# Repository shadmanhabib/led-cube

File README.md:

# LED-Cube
Repository of LED Cube project.

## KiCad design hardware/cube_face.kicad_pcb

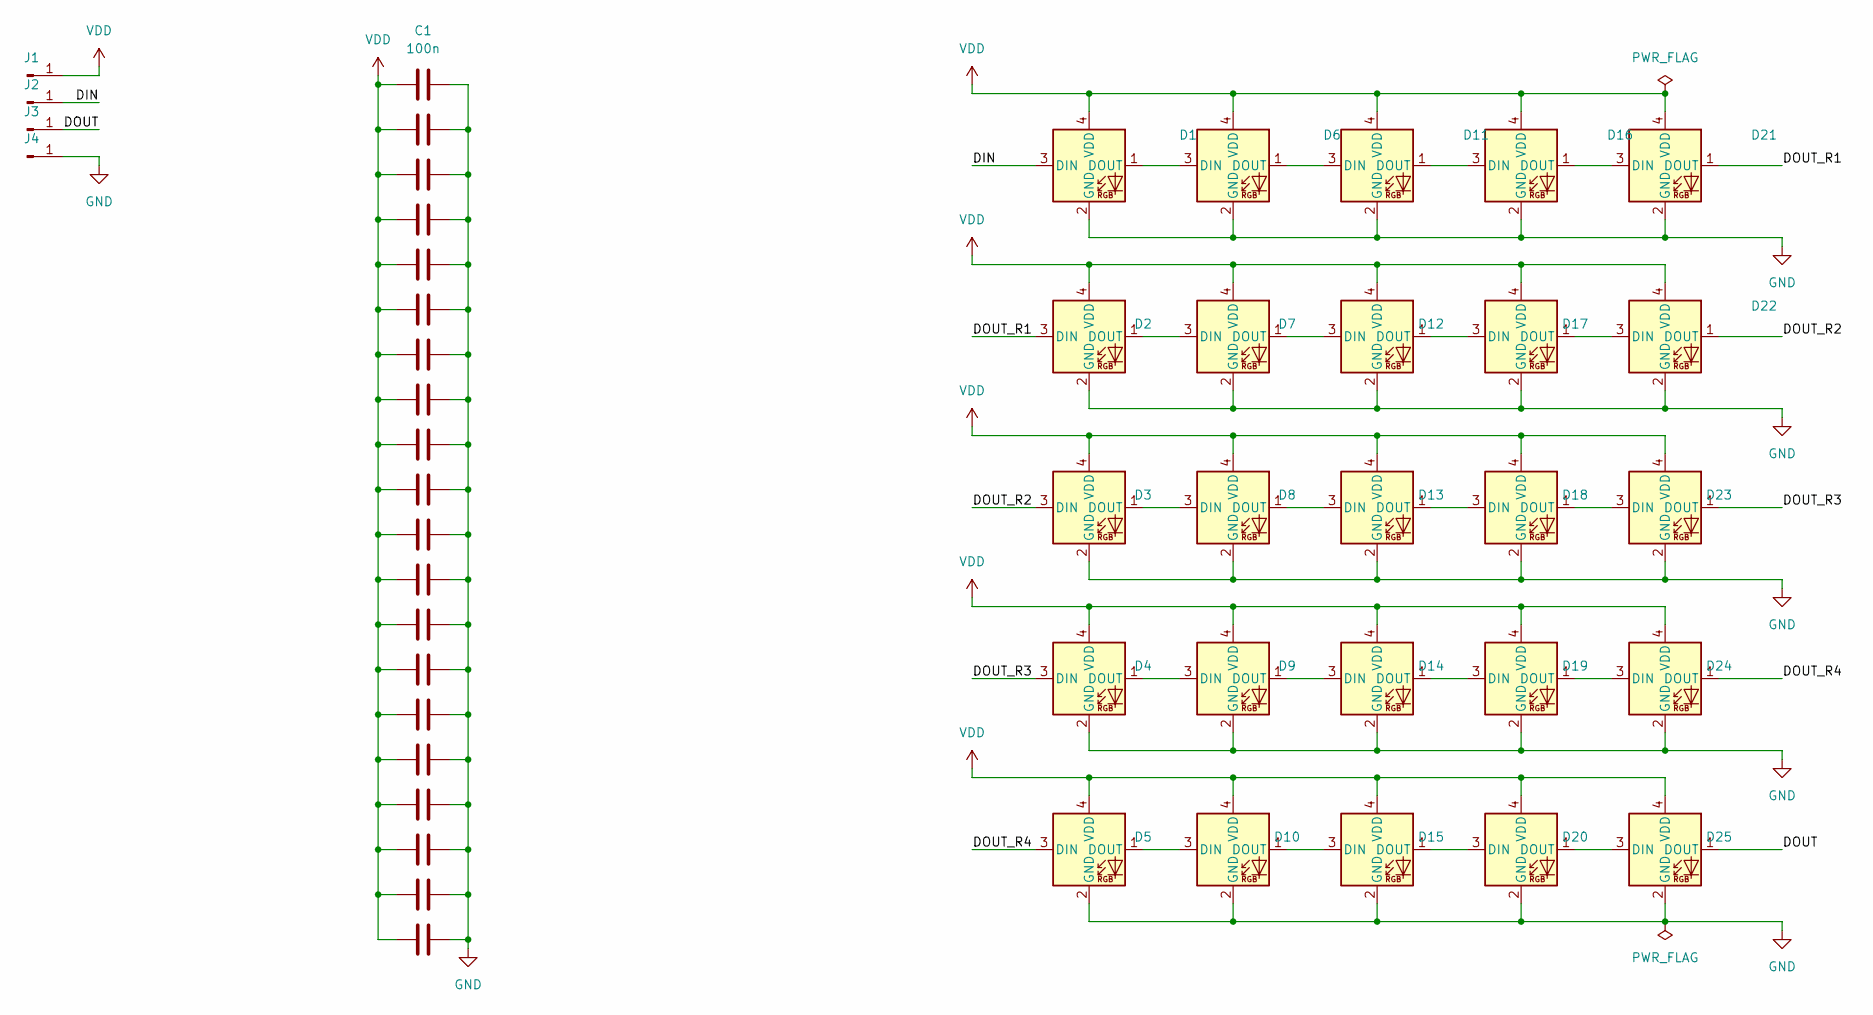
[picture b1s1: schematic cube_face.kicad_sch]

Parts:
C1, C2, C3, C4, C5, C6, C7, C8, C9, C10, C11, C12, C13, C14, C15, C16, C17, C18, C19, C20: 100n; C_0603_1608Metric
D1, D2, D3, D4, D5, D6, D7, D8, D9, D10, D11, D12, D13, D14, D15, D16, D17, D18, D19, D20, D21, D22, D23, D24, D25: WS2812B-2020
J1, J2, J3, J4: Conn_01x01_Male; SolderWirePad_1x01_SMD_5x10mm

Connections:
/DIN: D1.3 (DIN), J2.1
/DOUT: D25.1 (DOUT), J3.1
/DOUT_R1: D2.3 (DIN), D21.1 (DOUT)
/DOUT_R2: D3.3 (DIN), D22.1 (DOUT)
/DOUT_R3: D4.3 (DIN), D23.1 (DOUT)
/DOUT_R4: D5.3 (DIN), D24.1 (DOUT)
GND: C1.2, C2.2, C3.2, C4.2, C5.2, C6.2, C7.2, C8.2, C9.2, C10.2, C11.2, C12.2, C13.2, C14.2, C15.2, C16.2, C17.2, C18.2, C19.2, C20.2, D1.2 (GND), D2.2 (GND), D3.2 (GND), D4.2 (GND), D5.2 (GND), D6.2 (GND), D7.2 (GND), D8.2 (GND), D9.2 (GND), D10.2 (GND), D11.2 (GND), D12.2 (GND), D13.2 (GND), D14.2 (GND), D15.2 (GND), D16.2 (GND), D17.2 (GND), D18.2 (GND), D19.2 (GND), D20.2 (GND), D21.2 (GND), D22.2 (GND), D23.2 (GND), D24.2 (GND), D25.2 (GND), J4.1
unnamed: D1.1 (DOUT), D6.3 (DIN)
unnamed: D2.1 (DOUT), D7.3 (DIN)
unnamed: D3.1 (DOUT), D8.3 (DIN)
unnamed: D4.1 (DOUT), D9.3 (DIN)
unnamed: D10.1 (DOUT), D15.3 (DIN)
unnamed: D5.1 (DOUT), D10.3 (DIN)
unnamed: D11.1 (DOUT), D16.3 (DIN)
unnamed: D6.1 (DOUT), D11.3 (DIN)
unnamed: D12.1 (DOUT), D17.3 (DIN)
unnamed: D7.1 (DOUT), D12.3 (DIN)
unnamed: D13.1 (DOUT), D18.3 (DIN)
unnamed: D8.1 (DOUT), D13.3 (DIN)
unnamed: D14.1 (DOUT), D19.3 (DIN)
unnamed: D9.1 (DOUT), D14.3 (DIN)
unnamed: D15.1 (DOUT), D20.3 (DIN)
unnamed: D16.1 (DOUT), D21.3 (DIN)
unnamed: D17.1 (DOUT), D22.3 (DIN)
unnamed: D18.1 (DOUT), D23.3 (DIN)
unnamed: D19.1 (DOUT), D24.3 (DIN)
unnamed: D20.1 (DOUT), D25.3 (DIN)
VDD: C1.1, C2.1, C3.1, C4.1, C5.1, C6.1, C7.1, C8.1, C9.1, C10.1, C11.1, C12.1, C13.1, C14.1, C15.1, C16.1, C17.1, C18.1, C19.1, C20.1, D1.4 (VDD), D2.4 (VDD), D3.4 (VDD), D4.4 (VDD), D5.4 (VDD), D6.4 (VDD), D7.4 (VDD), D8.4 (VDD), D9.4 (VDD), D10.4 (VDD), D11.4 (VDD), D12.4 (VDD), D13.4 (VDD), D14.4 (VDD), D15.4 (VDD), D16.4 (VDD), D17.4 (VDD), D18.4 (VDD), D19.4 (VDD), D20.4 (VDD), D21.4 (VDD), D22.4 (VDD), D23.4 (VDD), D24.4 (VDD), D25.4 (VDD), J1.1

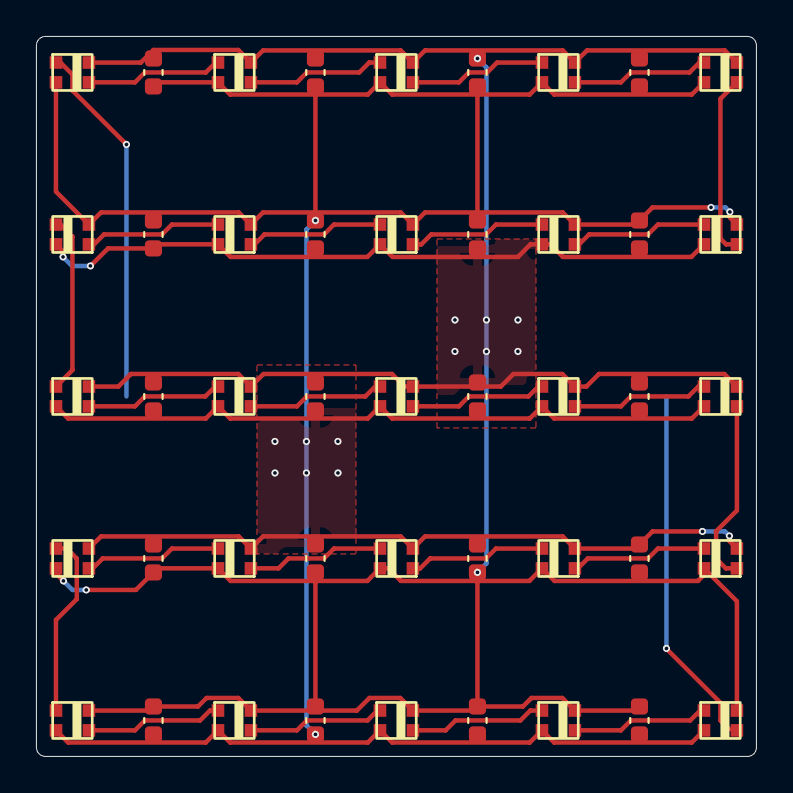
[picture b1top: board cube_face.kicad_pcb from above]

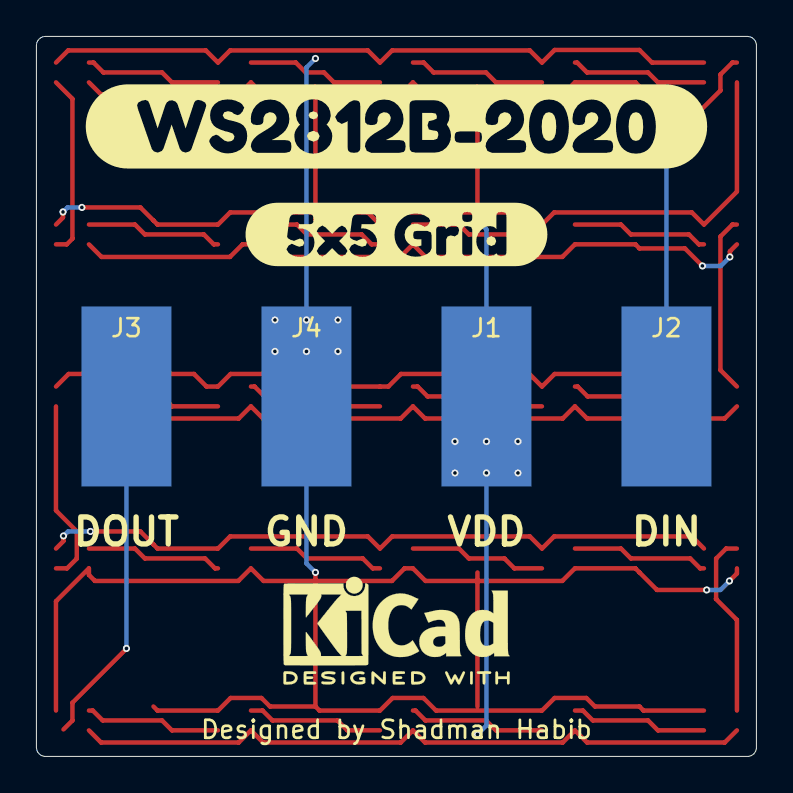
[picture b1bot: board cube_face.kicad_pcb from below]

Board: 2 copper layers, 40.0 x 40.0 mm, 51 parts (6 on the bottom side), 28 nets.

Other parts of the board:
kibuzzard-6351D6C0: G***; kibuzzard-6351D6C0
kibuzzard-6351D6F9: G***; kibuzzard-6351D6F9

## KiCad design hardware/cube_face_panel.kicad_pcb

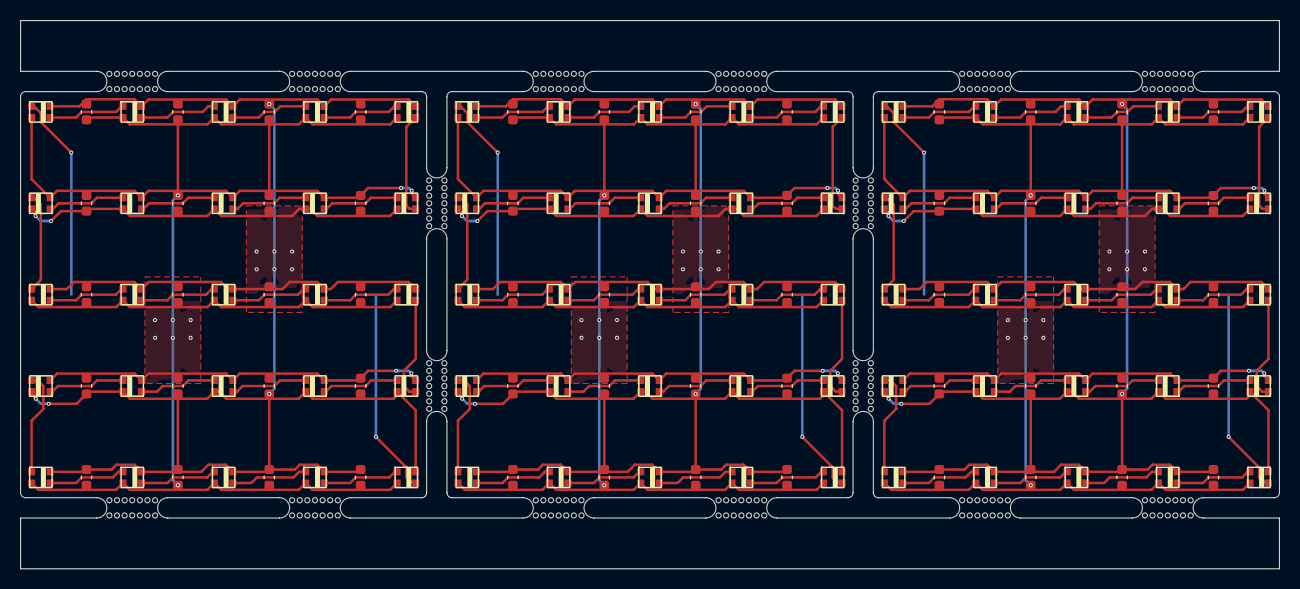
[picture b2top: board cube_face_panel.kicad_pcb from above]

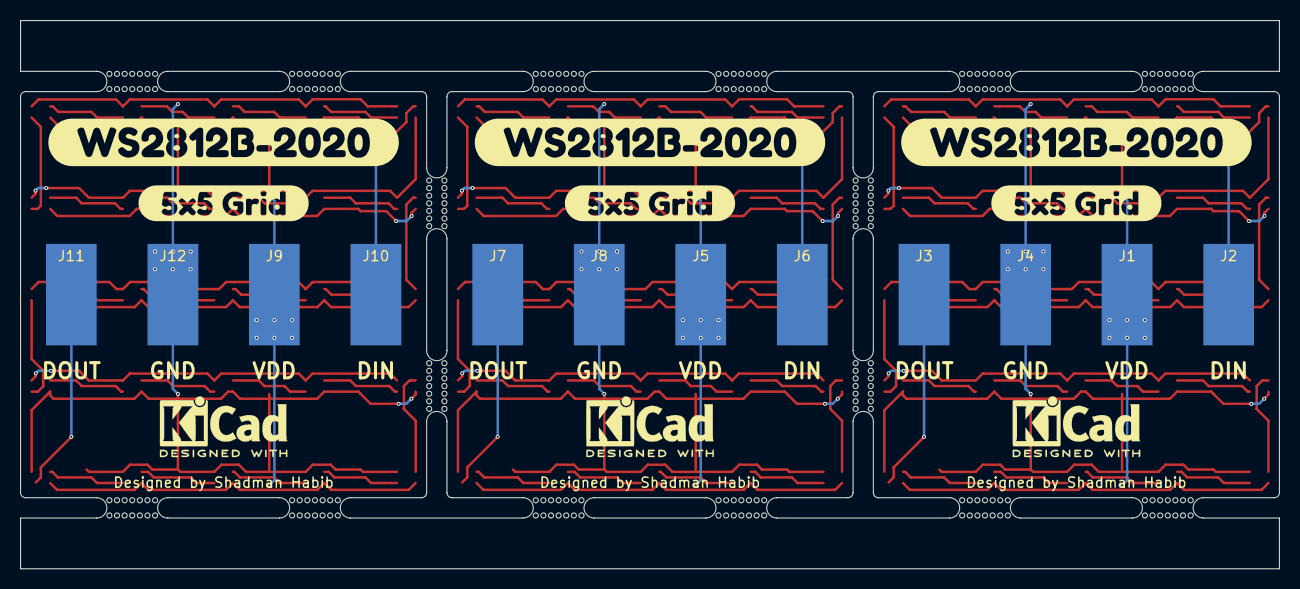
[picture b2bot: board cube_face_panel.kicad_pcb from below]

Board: 2 copper layers, 124.0 x 54.0 mm, 169 parts (18 on the bottom side), 28 nets.

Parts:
C1, C2, C3, C4, C5, C6, C7, C8, C9, C10, C11, C12, C13, C14, C15, C16, C17, C18, C19, C20, C21, C22, C23, C24, C25, C26, C27, C28, C29, C30, C31, C32, C33, C34, C35, C36, C37, C38, C39, C40, C41, C42, C43, C44, C45, C46, C47, C48, C49, C50, C51, C52, C53, C54, C55, C56, C57, C58, C59, C60: 100n; C_0603_1608Metric
D1, D2, D3, D4, D5, D6, D7, D8, D9, D10, D11, D12, D13, D14, D15, D16, D17, D18, D19, D20, D21, D22, D23, D24, D25, D26, D27, D28, D29, D30, D31, D32, D33, D34, D35, D36, D37, D38, D39, D40, D41, D42, D43, D44, D45, D46, D47, D48, D49, D50, D51, D52, D53, D54, D55, D56, D57, D58, D59, D60, D61, D62, D63, D64, D65, D66, D67, D68, D69, D70, D71, D72, D73, D74, D75: WS2812B-2020
J1, J2, J3, J4, J5, J6, J7, J8, J9, J10, J11, J12: Conn_01x01_Male; SolderWirePad_1x01_SMD_5x10mm
kibuzzard-6351D6C0, kibuzzard-6351D6C1, kibuzzard-6351D6C2: G***; kibuzzard-6351D6C0
kibuzzard-6351D6F1, kibuzzard-6351D6F2, kibuzzard-6351D6F9: G***; kibuzzard-6351D6F9
mouse-bite-2mm-slot, mouse-bite-2mm-slot#2, mouse-bite-2mm-slot#3, mouse-bite-2mm-slot#4, mouse-bite-2mm-slot#5, mouse-bite-2mm-slot#6, mouse-bite-2mm-slot#7, mouse-bite-2mm-slot#8, mouse-bite-2mm-slot#9, mouse-bite-2mm-slot#10, mouse-bite-2mm-slot#11, mouse-bite-2mm-slot#12, mouse-bite-2mm-slot#13, mouse-bite-2mm-slot#14, mouse-bite-2mm-slot#15, mouse-bite-2mm-slot#16: VAL**; mouse-bite-2mm-slot

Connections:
/DIN: D1.3 (DIN), D26.3 (DIN), D51.3 (DIN), J2.1, J6.1, J10.1
/DOUT: D25.1 (DOUT), D50.1 (DOUT), D75.1 (DOUT), J3.1, J7.1, J11.1
/DOUT_R1: D2.3 (DIN), D21.1 (DOUT), D27.3 (DIN), D46.1 (DOUT), D52.3 (DIN), D71.1 (DOUT)
/DOUT_R2: D3.3 (DIN), D22.1 (DOUT), D28.3 (DIN), D47.1 (DOUT), D53.3 (DIN), D72.1 (DOUT)
/DOUT_R3: D4.3 (DIN), D23.1 (DOUT), D29.3 (DIN), D48.1 (DOUT), D54.3 (DIN), D73.1 (DOUT)
/DOUT_R4: D5.3 (DIN), D24.1 (DOUT), D30.3 (DIN), D49.1 (DOUT), D55.3 (DIN), D74.1 (DOUT)
GND: C1.2, C2.2, C3.2, C4.2, C5.2, C6.2, C7.2, C8.2, C9.2, C10.2, C11.2, C12.2, C13.2, C14.2, C15.2, C16.2, C17.2, C18.2, C19.2, C20.2, C21.2, C22.2, C23.2, C24.2, C25.2, C26.2, C27.2, C28.2, C29.2, C30.2, C31.2, C32.2, C33.2, C34.2, C35.2, C36.2, C37.2, C38.2, C39.2, C40.2, C41.2, C42.2, C43.2, C44.2, C45.2, C46.2, C47.2, C48.2, C49.2, C50.2, C51.2, C52.2, C53.2, C54.2, C55.2, C56.2, C57.2, C58.2, C59.2, C60.2, D1.2 (GND), D2.2 (GND), D3.2 (GND), D4.2 (GND), D5.2 (GND), D6.2 (GND), D7.2 (GND), D8.2 (GND), D9.2 (GND), D10.2 (GND), D11.2 (GND), D12.2 (GND), D13.2 (GND), D14.2 (GND), D15.2 (GND), D16.2 (GND), D17.2 (GND), D18.2 (GND), D19.2 (GND), D20.2 (GND), D21.2 (GND), D22.2 (GND), D23.2 (GND), D24.2 (GND), D25.2 (GND), D26.2 (GND), D27.2 (GND), D28.2 (GND), D29.2 (GND), D30.2 (GND), D31.2 (GND), D32.2 (GND), D33.2 (GND), D34.2 (GND), D35.2 (GND), D36.2 (GND), D37.2 (GND), D38.2 (GND), D39.2 (GND), D40.2 (GND), D41.2 (GND), D42.2 (GND), D43.2 (GND), D44.2 (GND), D45.2 (GND), D46.2 (GND), D47.2 (GND), D48.2 (GND), D49.2 (GND), D50.2 (GND), D51.2 (GND), D52.2 (GND), D53.2 (GND), D54.2 (GND), D55.2 (GND), D56.2 (GND), D57.2 (GND), D58.2 (GND), D59.2 (GND), D60.2 (GND), D61.2 (GND), D62.2 (GND), D63.2 (GND), D64.2 (GND), D65.2 (GND), D66.2 (GND), D67.2 (GND), D68.2 (GND), D69.2 (GND), D70.2 (GND), D71.2 (GND), D72.2 (GND), D73.2 (GND), D74.2 (GND), D75.2 (GND), J4.1, J8.1, J12.1
unnamed: D1.1 (DOUT), D6.3 (DIN), D26.1 (DOUT), D31.3 (DIN), D51.1 (DOUT), D56.3 (DIN)
unnamed: D2.1 (DOUT), D7.3 (DIN), D27.1 (DOUT), D32.3 (DIN), D52.1 (DOUT), D57.3 (DIN)
unnamed: D3.1 (DOUT), D8.3 (DIN), D28.1 (DOUT), D33.3 (DIN), D53.1 (DOUT), D58.3 (DIN)
unnamed: D4.1 (DOUT), D9.3 (DIN), D29.1 (DOUT), D34.3 (DIN), D54.1 (DOUT), D59.3 (DIN)
unnamed: D10.1 (DOUT), D15.3 (DIN), D35.1 (DOUT), D40.3 (DIN), D60.1 (DOUT), D65.3 (DIN)
unnamed: D5.1 (DOUT), D10.3 (DIN), D30.1 (DOUT), D35.3 (DIN), D55.1 (DOUT), D60.3 (DIN)
unnamed: D11.1 (DOUT), D16.3 (DIN), D36.1 (DOUT), D41.3 (DIN), D61.1 (DOUT), D66.3 (DIN)
unnamed: D6.1 (DOUT), D11.3 (DIN), D31.1 (DOUT), D36.3 (DIN), D56.1 (DOUT), D61.3 (DIN)
unnamed: D12.1 (DOUT), D17.3 (DIN), D37.1 (DOUT), D42.3 (DIN), D62.1 (DOUT), D67.3 (DIN)
unnamed: D7.1 (DOUT), D12.3 (DIN), D32.1 (DOUT), D37.3 (DIN), D57.1 (DOUT), D62.3 (DIN)
unnamed: D13.1 (DOUT), D18.3 (DIN), D38.1 (DOUT), D43.3 (DIN), D63.1 (DOUT), D68.3 (DIN)
unnamed: D8.1 (DOUT), D13.3 (DIN), D33.1 (DOUT), D38.3 (DIN), D58.1 (DOUT), D63.3 (DIN)
unnamed: D14.1 (DOUT), D19.3 (DIN), D39.1 (DOUT), D44.3 (DIN), D64.1 (DOUT), D69.3 (DIN)
unnamed: D9.1 (DOUT), D14.3 (DIN), D34.1 (DOUT), D39.3 (DIN), D59.1 (DOUT), D64.3 (DIN)
unnamed: D15.1 (DOUT), D20.3 (DIN), D40.1 (DOUT), D45.3 (DIN), D65.1 (DOUT), D70.3 (DIN)
unnamed: D16.1 (DOUT), D21.3 (DIN), D41.1 (DOUT), D46.3 (DIN), D66.1 (DOUT), D71.3 (DIN)
unnamed: D17.1 (DOUT), D22.3 (DIN), D42.1 (DOUT), D47.3 (DIN), D67.1 (DOUT), D72.3 (DIN)
unnamed: D18.1 (DOUT), D23.3 (DIN), D43.1 (DOUT), D48.3 (DIN), D68.1 (DOUT), D73.3 (DIN)
unnamed: D19.1 (DOUT), D24.3 (DIN), D44.1 (DOUT), D49.3 (DIN), D69.1 (DOUT), D74.3 (DIN)
unnamed: D20.1 (DOUT), D25.3 (DIN), D45.1 (DOUT), D50.3 (DIN), D70.1 (DOUT), D75.3 (DIN)
VDD: C1.1, C2.1, C3.1, C4.1, C5.1, C6.1, C7.1, C8.1, C9.1, C10.1, C11.1, C12.1, C13.1, C14.1, C15.1, C16.1, C17.1, C18.1, C19.1, C20.1, C21.1, C22.1, C23.1, C24.1, C25.1, C26.1, C27.1, C28.1, C29.1, C30.1, C31.1, C32.1, C33.1, C34.1, C35.1, C36.1, C37.1, C38.1, C39.1, C40.1, C41.1, C42.1, C43.1, C44.1, C45.1, C46.1, C47.1, C48.1, C49.1, C50.1, C51.1, C52.1, C53.1, C54.1, C55.1, C56.1, C57.1, C58.1, C59.1, C60.1, D1.4 (VDD), D2.4 (VDD), D3.4 (VDD), D4.4 (VDD), D5.4 (VDD), D6.4 (VDD), D7.4 (VDD), D8.4 (VDD), D9.4 (VDD), D10.4 (VDD), D11.4 (VDD), D12.4 (VDD), D13.4 (VDD), D14.4 (VDD), D15.4 (VDD), D16.4 (VDD), D17.4 (VDD), D18.4 (VDD), D19.4 (VDD), D20.4 (VDD), D21.4 (VDD), D22.4 (VDD), D23.4 (VDD), D24.4 (VDD), D25.4 (VDD), D26.4 (VDD), D27.4 (VDD), D28.4 (VDD), D29.4 (VDD), D30.4 (VDD), D31.4 (VDD), D32.4 (VDD), D33.4 (VDD), D34.4 (VDD), D35.4 (VDD), D36.4 (VDD), D37.4 (VDD), D38.4 (VDD), D39.4 (VDD), D40.4 (VDD), D41.4 (VDD), D42.4 (VDD), D43.4 (VDD), D44.4 (VDD), D45.4 (VDD), D46.4 (VDD), D47.4 (VDD), D48.4 (VDD), D49.4 (VDD), D50.4 (VDD), D51.4 (VDD), D52.4 (VDD), D53.4 (VDD), D54.4 (VDD), D55.4 (VDD), D56.4 (VDD), D57.4 (VDD), D58.4 (VDD), D59.4 (VDD), D60.4 (VDD), D61.4 (VDD), D62.4 (VDD), D63.4 (VDD), D64.4 (VDD), D65.4 (VDD), D66.4 (VDD), D67.4 (VDD), D68.4 (VDD), D69.4 (VDD), D70.4 (VDD), D71.4 (VDD), D72.4 (VDD), D73.4 (VDD), D74.4 (VDD), D75.4 (VDD), J1.1, J5.1, J9.1

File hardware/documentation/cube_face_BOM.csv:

Comment,Designator,Footprint,LCSC
100n,"C1,C2,C3,C4,C5,C6,C7,C8,C9,C10,C11,C12,C13,C14,C15,C16,C17,C18,C19,C20,C21,C22,C23,C24,C25,C26,C27,C28,C29,C30,C31,C32,C33,C34,C35,C36,C37,C38,C39,C40,C41,C42,C43,C44,C45,C46,C47,C48,C49,C50,C51,C52,C53,C54,C55,C56,C57,C58,C59,C60",Capacitor_SMD:C_0603_1608Metric,C14663
WS2812B-2020,"D1,D2,D3,D4,D5,D6,D7,D8,D9,D10,D11,D12,D13,D14,D15,D16,D17,D18,D19,D20,D21,D22,D23,D24,D25,D26,D27,D28,D29,D30,D31,D32,D33,D34,D35,D36,D37,D38,D39,D40,D41,D42,D43,D44,D45,D46,D47,D48,D49,D50,D51,D52,D53,D54,D55,D56,D57,D58,D59,D60,D61,D62,D63,D64,D65,D66,D67,D68,D69,D70,D71,D72,D73,D74,D75",WS2812B-2020:WS2812B-2020,C965555

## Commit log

2022-11-30 Set folder structure
    Copied folder structure from template.
2022-11-30 Removed .DS_Store
    Removes .DS_Store files from repo.
2022-12-01 Commit files
    Commit of all files relating to the LED Cube project. This includes
    CAD models and PCB design and fabrication files.
